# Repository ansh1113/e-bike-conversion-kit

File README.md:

# e-Bike Conversion Kit

## Overview
This project is a custom e-bike conversion kit featuring:
- **STM32-based VESC ESC** for motor control
- **ESP32/ESP8266** for wireless control and battery monitoring
- **36V 10.4Ah Lithium Power Supply** with buck circuits (36V->24V, 24V->12V, 12V->5V)
- **Wireless throttle module** (mode increase/decrease/start switches)
- **GSM/GPS integration** for tracking and security
- **Battery level and mode indicator LEDs**
- **Electronic latch locking system**
- **Phone charging port**

## Features
- Wireless throttle control using ESP32
- Real-time battery monitoring and motor control
- GPS tracking for security
- Compact 4-layer PCB design

## Installation
## 1. Hardware Assembly
- Mount the **VESC ESC** with proper cooling.
- Connect the **36V battery** to the power input.
- Wire the **ESP module** to the ESC for PPM signal transmission.
- Connect **buck converters** for proper voltage regulation.
- Attach **LEDs**, **GSM/GPS module**, and **gyro sensor**.
- Install **wireless throttle module** on the handlebar.

## 2. Software Setup
- Install **VESC Tool** for ESC configuration.
- Flash the **ESP firmware** using Arduino IDE.
- Configure **PPM values** for different speed modes.

# Firmware Installation
## 1. Flashing VESC Firmware
- Download and install **VESC Tool**.
- Connect STM32 to your PC via USB.
- Select the correct **firmware version** and upload.

## 2. Flashing ESP Firmware
- Install **Arduino IDE** with ESP32/ESP8266 support.
- Install necessary libraries (`WiFi`, `TinyGPS++`, `Adafruit_GFX` etc.).
- Compile and upload `Firmware/hook_receiver/hook_receiver.ino`.

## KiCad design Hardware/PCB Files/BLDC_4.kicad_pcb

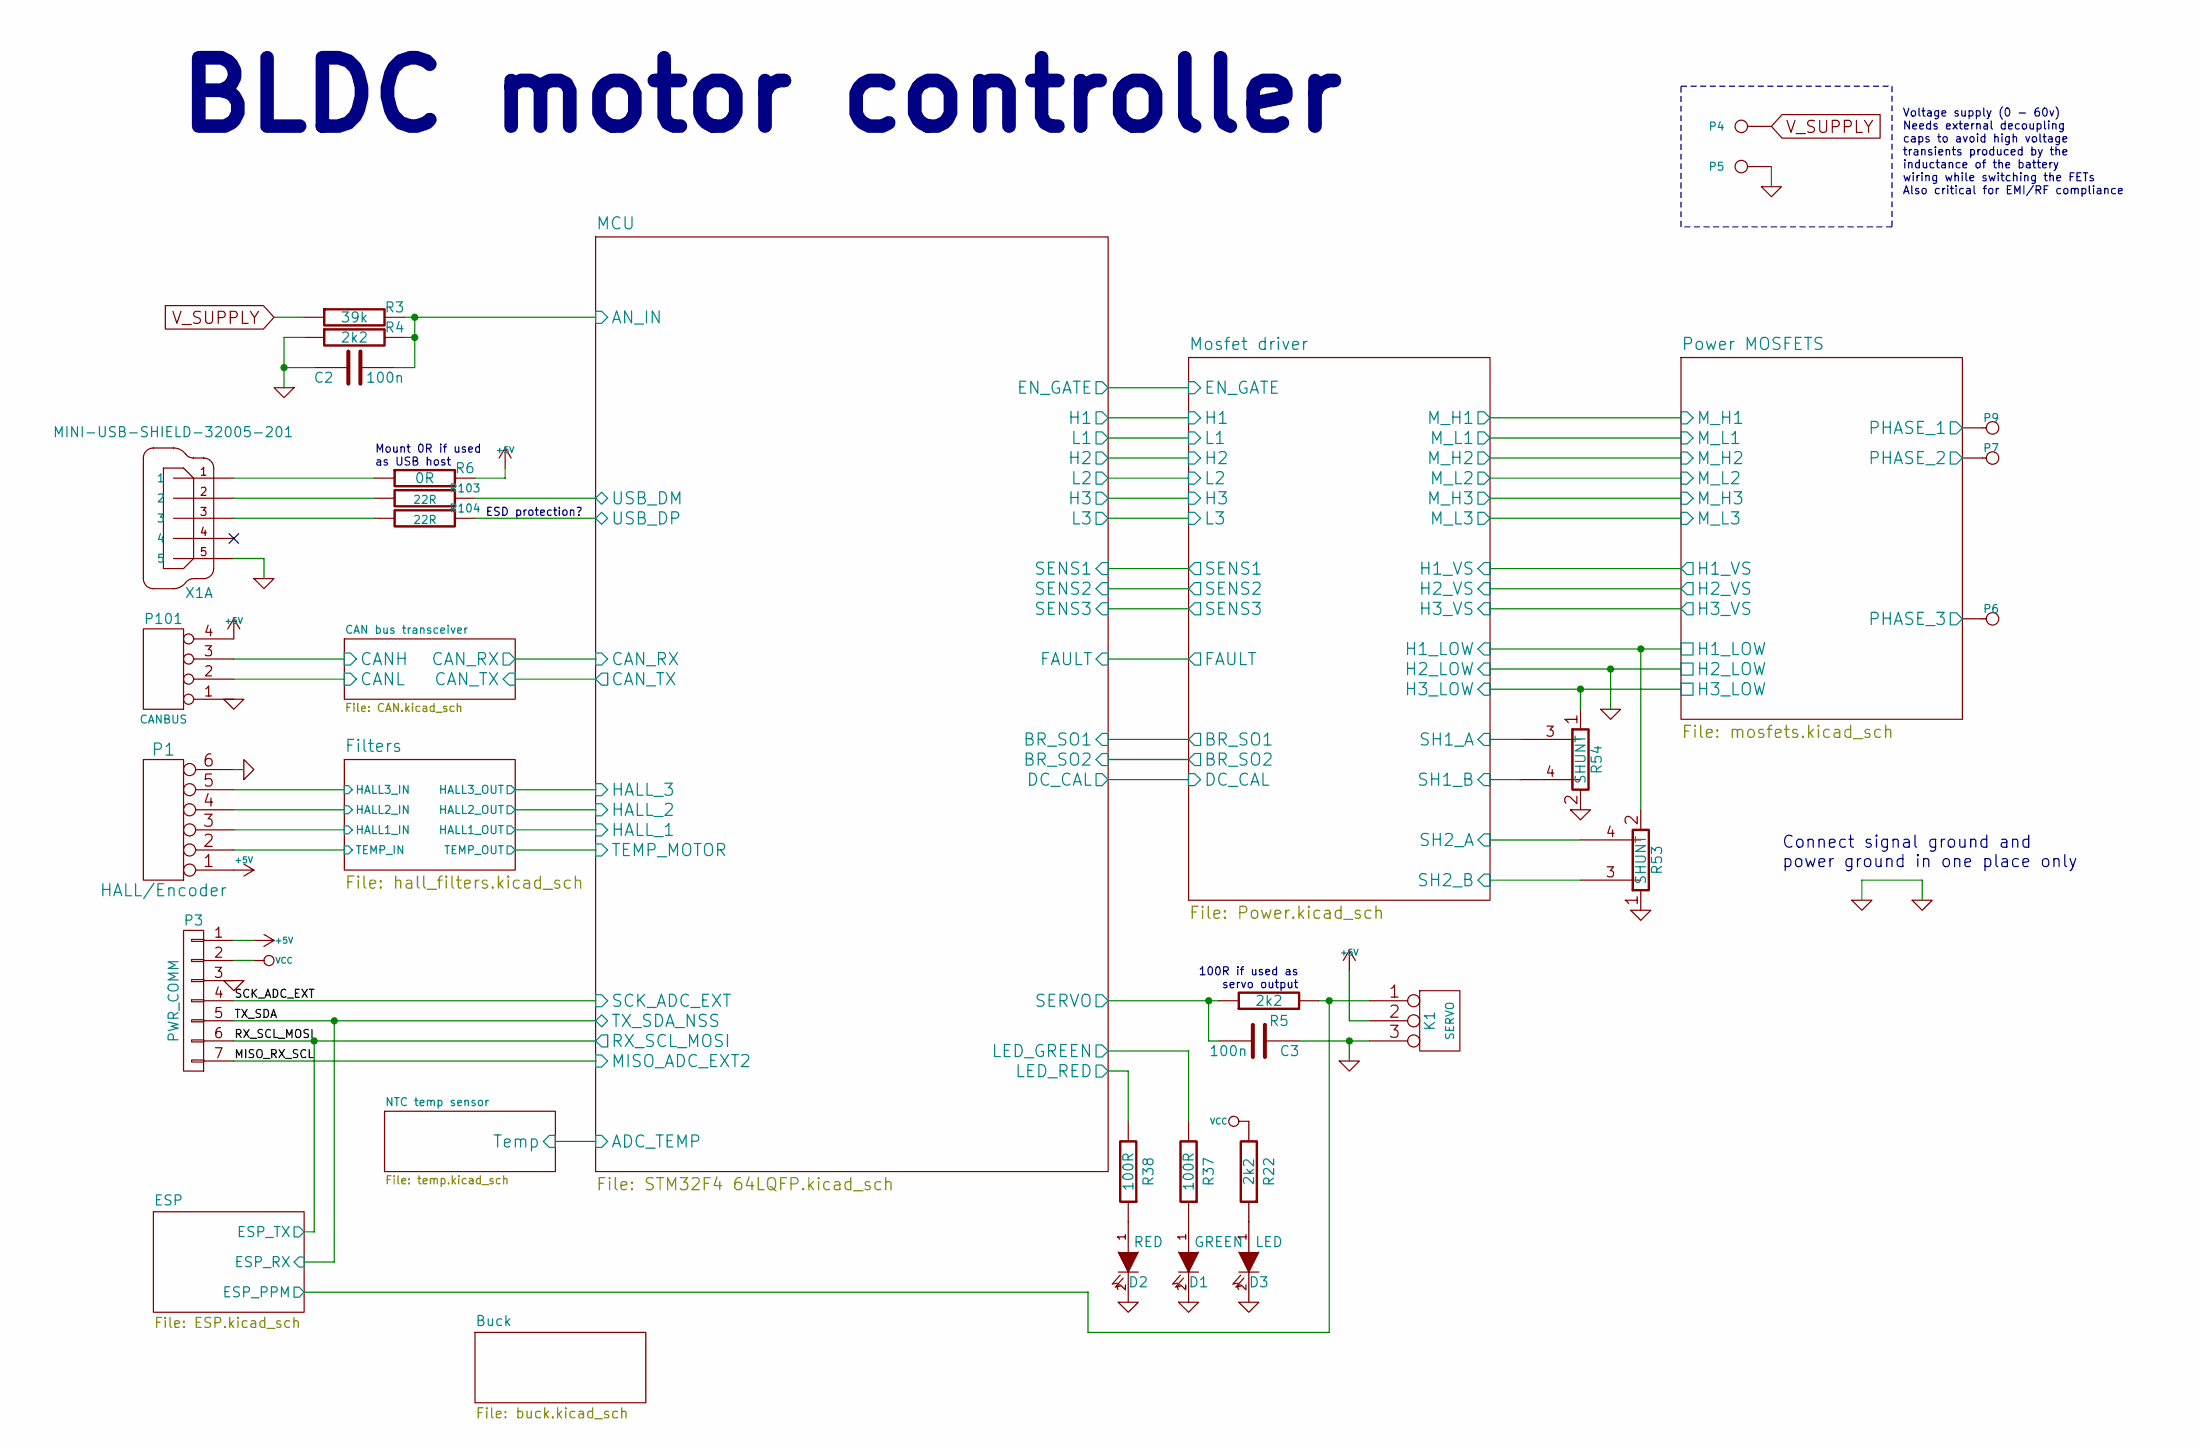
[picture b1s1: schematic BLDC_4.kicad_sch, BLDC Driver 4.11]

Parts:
C2, C3: 100n; SMD-0603_c
D1: GREEN; LED-0603
D2: RED; LED-0603
D3: LED; LED-0603
K1: SERVO; pinhead-1X03
P1: HALL/Encoder; MICRO_JST_6
P3: PWR_COMM; b7b-ph-kl
P4: IN+; 1PAD_4x5mm
P5: IN-; 1PAD_4x5mm
P6: MOTOR1; 1PAD_4x5mm
P7: MOTOR2; 1PAD_4x5mm
P9: MOTOR3; 1PAD_4x5mm
P101: CANBUS; b4b-ph-kl
R3: 39k; SMD-0603_r
R4, R5, R22: 2k2; SMD-0603_r
R6: 0R; SMD-0603_r
R37, R38: 100R; SMD-0603_r
R53, R54: SHUNT; WSLP2726
R103, R104: 22R; SMD-0603_r
X1: MINI-USB-SHIELD-32005-201; USB-UX60R-MB-5ST

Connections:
+5V: K1.2 (PM), P1.1, P3.1, P101.4, R6.2; also elsewhere on the board
/CAN bus transceiver/CANH: P101.3; also elsewhere on the board
/CAN bus transceiver/CANL: P101.2; also elsewhere on the board
/ESP/ESP_PPM: K1.1, R5.2; also elsewhere on the board
/Filters/HALL1_IN: P1.3; also elsewhere on the board
/Filters/HALL2_IN: P1.4; also elsewhere on the board
/Filters/HALL3_IN: P1.5; also elsewhere on the board
/Filters/TEMP_MOTOR: P1.2; also elsewhere on the board
/MCU/AN_IN: C2.2, R3.2, R4.2; also elsewhere on the board
/MCU/LED_GREEN: R37.2; also elsewhere on the board
/MCU/LED_RED: R38.2; also elsewhere on the board
/MCU/SERVO: C3.2, R5.1; also elsewhere on the board
/MCU/USB_DM: R103.1; also elsewhere on the board
/MCU/USB_DP: R104.1; also elsewhere on the board
/MISO_RX_SCL: P3.7; also elsewhere on the board
/Mosfet driver/H1_LOW: R53.2; also elsewhere on the board
/Mosfet driver/H1_VS: P9.1; also elsewhere on the board
/Mosfet driver/H2_VS: P7.1; also elsewhere on the board
/Mosfet driver/H3_LOW: R54.1; also elsewhere on the board
/Mosfet driver/H3_VS: P6.1; also elsewhere on the board
/Mosfet driver/SH1_A: R54.3; also elsewhere on the board
/Mosfet driver/SH1_B: R54.4; also elsewhere on the board
/Mosfet driver/SH2_A: R53.4; also elsewhere on the board
/Mosfet driver/SH2_B: R53.3; also elsewhere on the board
/RX_SCL_MOSI: P3.6; also elsewhere on the board
/SCK_ADC_EXT: P3.4; also elsewhere on the board
/TX_SDA: P3.5; also elsewhere on the board
GND: C2.1, C3.1, D1.2 (K), D2.2 (K), D3.2 (K), K1.3, P1.6, P3.3, P5.1, P101.1, R4.1, R53.1, R54.2, X1.5; also elsewhere on the board
unnamed: D1.1 (A), R37.1
unnamed: D2.1 (A), R38.1
unnamed: D3.1 (A), R22.1
unnamed: R6.1, X1.1
unnamed: R103.2, X1.2
unnamed: R104.2, X1.3
VCC: P3.2, R22.2; also elsewhere on the board
V_SUPPLY: P4.1, R3.1; also elsewhere on the board

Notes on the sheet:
Voltage supply (0 - 60v) Needs external decoupling caps to avoid high voltage transients produced by the inductance of the battery wiring while switching the FETs Also critical for EMI/RF compliance
100R if used as servo output
Mount 0R if used as USB host
BLDC motor controller
Connect signal ground and power ground in one place only
ESD protection?

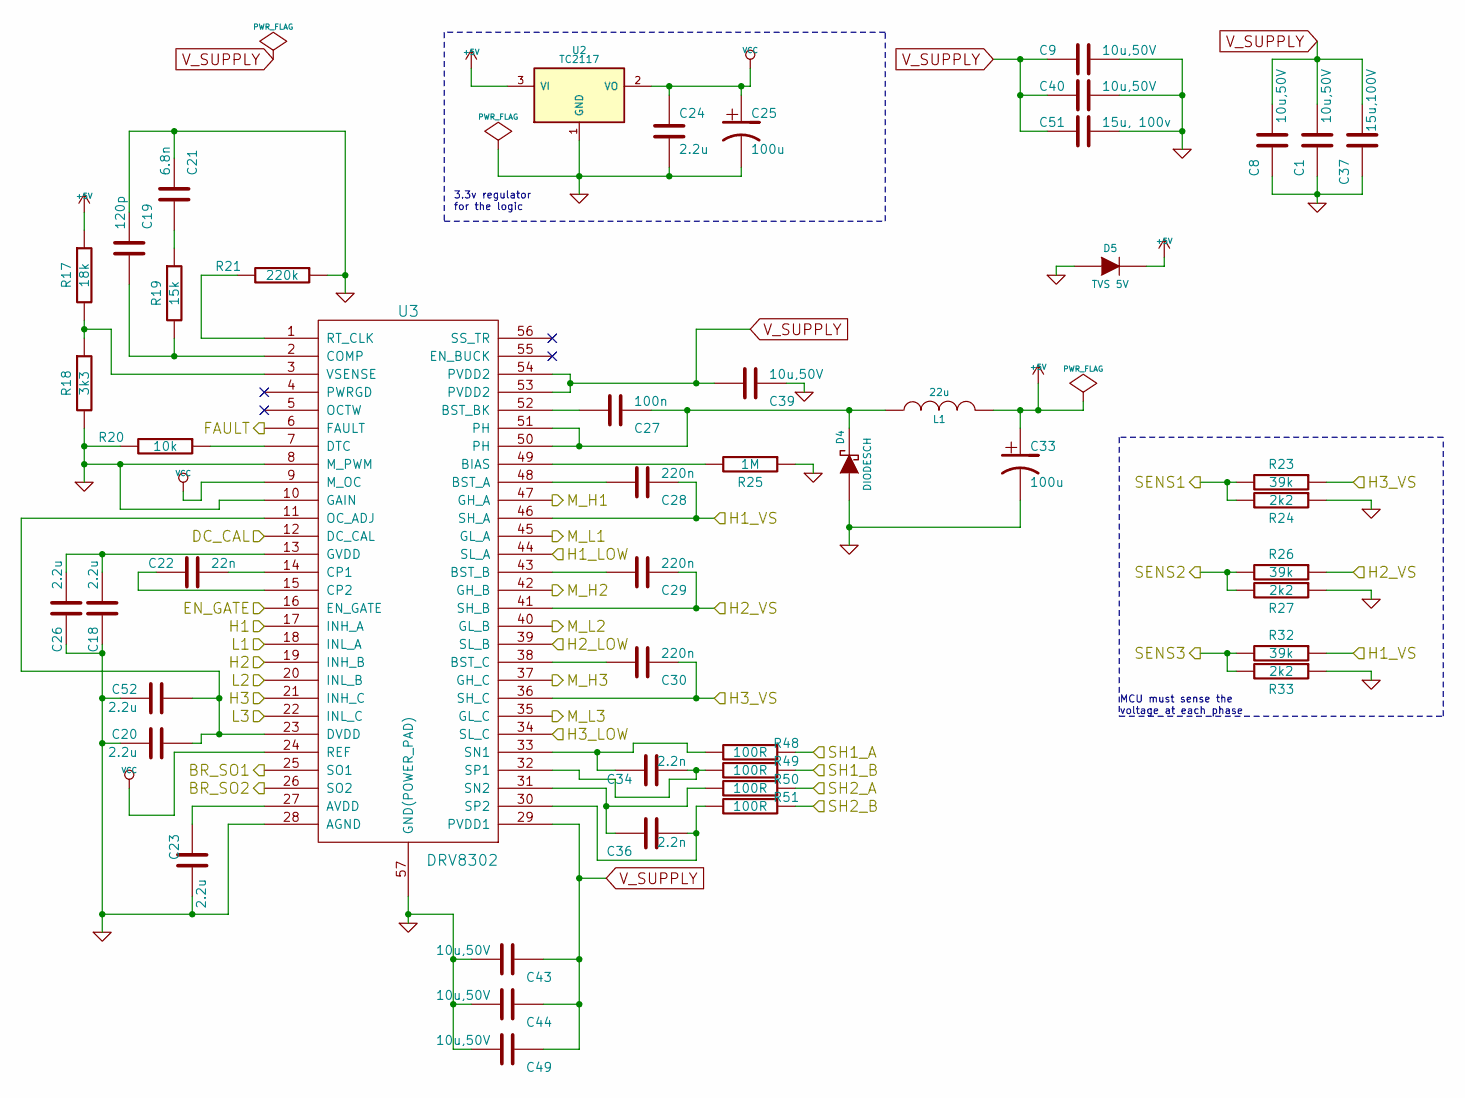
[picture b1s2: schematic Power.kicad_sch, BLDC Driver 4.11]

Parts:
C1, C8, C9, C39, C40, C43, C44, C49: 10u,50V; SMD-1206
C18, C20, C23, C24, C26, C52: 2.2u; SMD-0603_c
C19: 120p; SMD-0603_c
C21: 6.8n; SMD-0603_c
C22: 22n; SMD-0603_c
C25, C33: 100u; c_tant_B
C27: 100n; SMD-0603_c
C28, C29, C30: 220n; SMD-0603_c
C34, C36: 2.2n; SMD-0603_c
C37: 15u,100V; c_2220
C51: 15u, 100v; c_2220
D4: DIODESCH; SMA_Handsoldering
D5: TVS 5V; do214ac
L1: 22u; inductor_smd_8x5mm
R17: 18k; SMD-0603_r
R18: 3k3; SMD-0603_r
R19: 15k; SMD-0603_r
R20: 10k; SMD-0603_r
R21: 220k; SMD-0603_r
R23, R26, R32: 39k; SMD-0603_r
R24, R27, R33: 2k2; SMD-0603_r
R25: 1M; SMD-0603_r
R48, R49, R50, R51: 100R; SMD-0603_r
U2: TC2117; SOT-223
U3: DRV8302; TSSOP-56-PP

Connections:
+5V: C33.1, D5.2 (K), L1.2, R17.1, U2.3 (VI); also elsewhere on the board
/MCU/BR_SO1: U3.25 (SO1); also elsewhere on the board
/MCU/BR_SO2: U3.26 (SO2); also elsewhere on the board
/MCU/DC_CAL: U3.12 (DC_CAL); also elsewhere on the board
/MCU/EN_GATE: U3.16 (EN_GATE); also elsewhere on the board
/MCU/FAULT: U3.6 (FAULT); also elsewhere on the board
/MCU/H1: U3.17 (INH_A); also elsewhere on the board
/MCU/H2: U3.19 (INH_B); also elsewhere on the board
/MCU/H3: U3.21 (INH_C); also elsewhere on the board
/MCU/L1: U3.18 (INL_A); also elsewhere on the board
/MCU/L2: U3.20 (INL_B); also elsewhere on the board
/MCU/L3: U3.22 (INL_C); also elsewhere on the board
/MCU/SENS1: R23.2, R24.2; also elsewhere on the board
/MCU/SENS2: R26.2, R27.2; also elsewhere on the board
/MCU/SENS3: R32.2, R33.2; also elsewhere on the board
/Mosfet driver/H1_LOW: U3.44 (SL_A); also elsewhere on the board
/Mosfet driver/H1_VS: C28.1, R32.1, U3.46 (SH_A); also elsewhere on the board
/Mosfet driver/H2_VS: C29.1, R26.1, U3.41 (SH_B); also elsewhere on the board
/Mosfet driver/H3_LOW: U3.34 (SL_C); also elsewhere on the board
/Mosfet driver/H3_VS: C30.1, R23.1, U3.36 (SH_C); also elsewhere on the board
/Mosfet driver/M_H1: U3.47 (GH_A); also elsewhere on the board
/Mosfet driver/M_H2: U3.42 (GH_B); also elsewhere on the board
/Mosfet driver/M_H3: U3.37 (GH_C); also elsewhere on the board
/Mosfet driver/M_L1: U3.45 (GL_A); also elsewhere on the board
/Mosfet driver/M_L2: U3.40 (GL_B); also elsewhere on the board
/Mosfet driver/M_L3: U3.35 (GL_C); also elsewhere on the board
/Mosfet driver/SH1_A: R48.1; also elsewhere on the board
/Mosfet driver/SH1_B: R49.1; also elsewhere on the board
/Mosfet driver/SH2_A: R50.1; also elsewhere on the board
/Mosfet driver/SH2_B: R51.1; also elsewhere on the board
GND: C1.1, C8.1, C9.1, C18.2, C19.1, C20.1, C21.1, C23.1, C24.2, C25.2, C26.2, C33.2, C37.1, C39.1, C40.1, C43.2, C44.2, C49.2, C51.1, C52.1, D4.1 (A), D5.1 (A), R18.2, R20.2, R21.1, R24.1, R25.1, R27.1, R33.1, U2.1 (GND), U3.8 (M_PWM), U3.10 (GAIN), U3.28 (AGND), U3.39 (SL_B), U3.57 (GND(POWER_PAD)); also elsewhere on the board
unnamed: C21.2, R19.1
unnamed: C27.1, D4.2 (K), L1.1, U3.50 (PH), U3.51 (PH)
unnamed: C23.2, U3.27 (AVDD)
unnamed: R25.2, U3.49 (BIAS)
unnamed: C28.2, U3.48 (BST_A)
unnamed: C29.2, U3.43 (BST_B)
unnamed: C27.2, U3.52 (BST_BK)
unnamed: C30.2, U3.38 (BST_C)
unnamed: C19.2, R19.2, U3.2 (COMP)
unnamed: C22.1, U3.14 (CP1)
unnamed: C22.2, U3.15 (CP2)
unnamed: R20.1, U3.7 (DTC)
unnamed: C20.2, C52.2, U3.11 (OC_ADJ), U3.23 (DVDD)
unnamed: C18.1, C26.1, U3.13 (GVDD)
unnamed: R21.2, U3.1 (RT_CLK)
unnamed: C34.1, R48.2, U3.33 (SN1)
unnamed: C36.1, R50.2, U3.31 (SN2)
unnamed: C34.2, R49.2, U3.32 (SP1)
unnamed: C36.2, R51.2, U3.30 (SP2)
unnamed: R17.2, R18.1, U3.3 (VSENSE)
VCC: C24.1, C25.1, U2.2 (VO), U3.9 (M_OC), U3.24 (REF); also elsewhere on the board
V_SUPPLY: C1.2, C8.2, C9.2, C37.2, C39.2, C40.2, C43.1, C44.1, C49.1, C51.2, U3.29 (PVDD1), U3.53 (PVDD2), U3.54 (PVDD2); also elsewhere on the board

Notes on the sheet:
3.3v regulator for the logic
MCU must sense the voltage at each phase

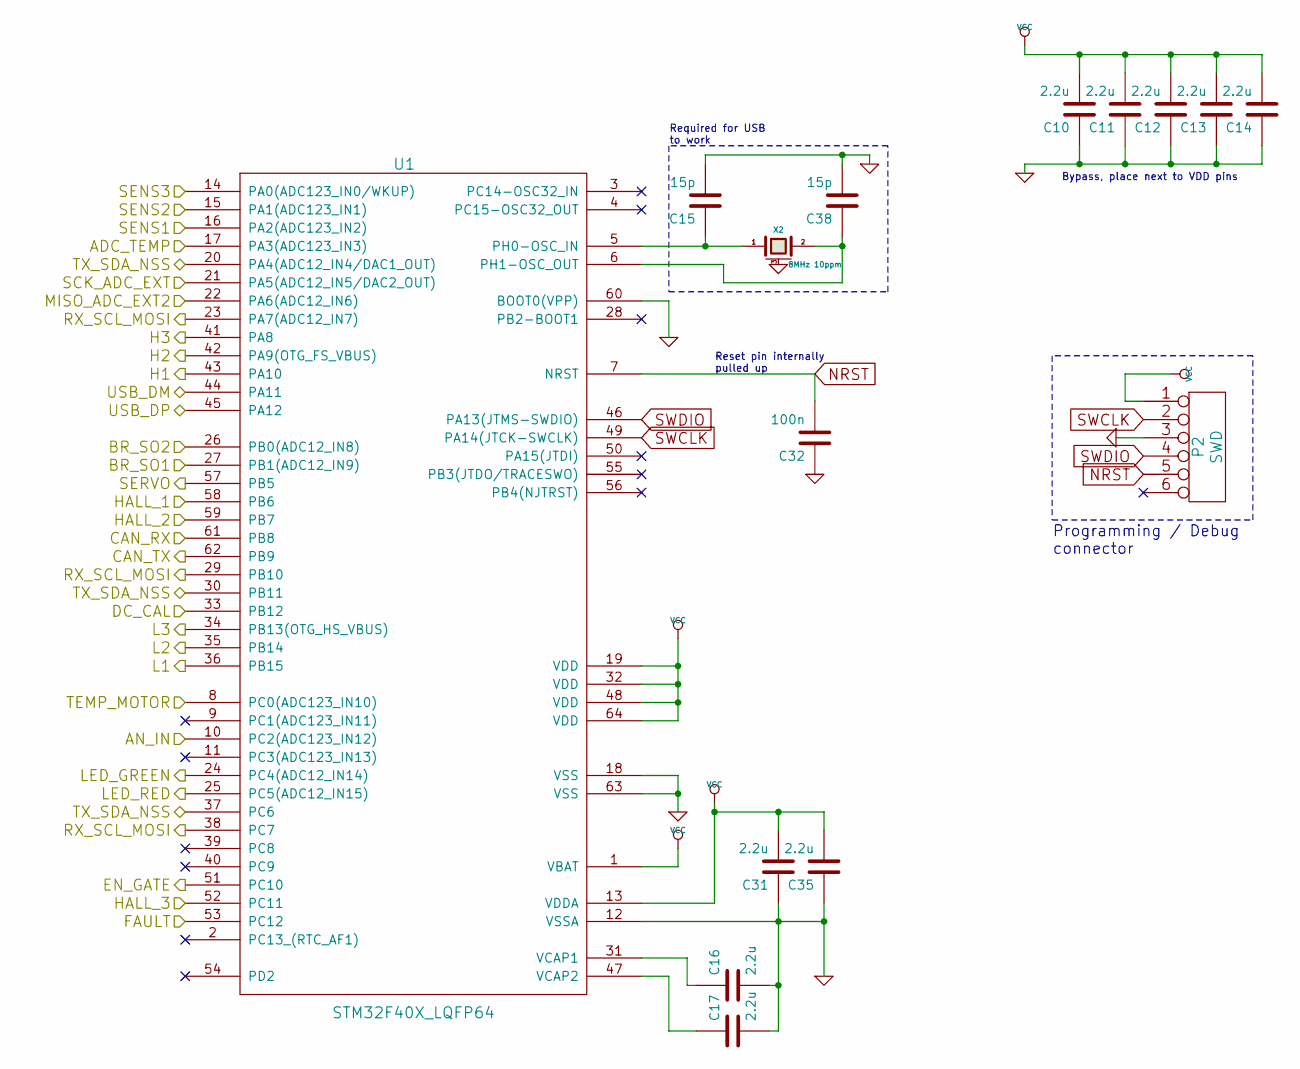
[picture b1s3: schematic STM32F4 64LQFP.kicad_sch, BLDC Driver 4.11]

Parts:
C10, C11, C12, C13, C14, C16, C17, C31, C35: 2.2u; SMD-0603_c
C15, C38: 15p; SMD-0603_c
C32: 100n; SMD-0603_c
P2: SWD; MICRO_JST_6
U1: STM32F40X_LQFP64; lqfp64_pad_mod
X2: 8MHz 10ppm; Crystal_5x3mm; mfg# ABM3B-8.0-10-1UT

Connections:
/CAN bus transceiver/CAN_RX: U1.61 (PB8); also elsewhere on the board
/CAN bus transceiver/CAN_TX: U1.62 (PB9); also elsewhere on the board
/Filters/HALL1_OUT: U1.58 (PB6); also elsewhere on the board
/Filters/HALL2_OUT: U1.59 (PB7); also elsewhere on the board
/Filters/HALL3_OUT: U1.52 (PC11); also elsewhere on the board
/Filters/TEMP_MOTOR: U1.8 (PC0(ADC123_IN10)); also elsewhere on the board
/MCU/ADC_TEMP: U1.17 (PA3(ADC123_IN3)); also elsewhere on the board
/MCU/AN_IN: U1.10 (PC2(ADC123_IN12)); also elsewhere on the board
/MCU/BR_SO1: U1.27 (PB1(ADC12_IN9)); also elsewhere on the board
/MCU/BR_SO2: U1.26 (PB0(ADC12_IN8)); also elsewhere on the board
/MCU/DC_CAL: U1.33 (PB12); also elsewhere on the board
/MCU/EN_GATE: U1.51 (PC10); also elsewhere on the board
/MCU/FAULT: U1.53 (PC12); also elsewhere on the board
/MCU/H1: U1.43 (PA10); also elsewhere on the board
/MCU/H2: U1.42 (PA9(OTG_FS_VBUS)); also elsewhere on the board
/MCU/H3: U1.41 (PA8); also elsewhere on the board
/MCU/L1: U1.36 (PB15); also elsewhere on the board
/MCU/L2: U1.35 (PB14); also elsewhere on the board
/MCU/L3: U1.34 (PB13(OTG_HS_VBUS)); also elsewhere on the board
/MCU/LED_GREEN: U1.24 (PC4(ADC12_IN14)); also elsewhere on the board
/MCU/LED_RED: U1.25 (PC5(ADC12_IN15)); also elsewhere on the board
/MCU/SENS1: U1.16 (PA2(ADC123_IN2)); also elsewhere on the board
/MCU/SENS2: U1.15 (PA1(ADC123_IN1)); also elsewhere on the board
/MCU/SENS3: U1.14 (PA0(ADC123_IN0/WKUP)); also elsewhere on the board
/MCU/SERVO: U1.57 (PB5); also elsewhere on the board
/MCU/USB_DM: U1.44 (PA11); also elsewhere on the board
/MCU/USB_DP: U1.45 (PA12); also elsewhere on the board
/MISO_RX_SCL: U1.22 (PA6(ADC12_IN6)); also elsewhere on the board
/RX_SCL_MOSI: U1.23 (PA7(ADC12_IN7)), U1.29 (PB10), U1.38 (PC7); also elsewhere on the board
/SCK_ADC_EXT: U1.21 (PA5(ADC12_IN5/DAC2_OUT)); also elsewhere on the board
/TX_SDA: U1.20 (PA4(ADC12_IN4/DAC1_OUT)), U1.30 (PB11), U1.37 (PC6); also elsewhere on the board
GND: C10.1, C11.1, C12.1, C13.1, C14.1, C15.2, C16.2, C17.2, C31.1, C32.1, C35.1, C38.2, P2.3, U1.12 (VSSA), U1.18 (VSS), U1.60 (BOOT0(VPP)), U1.63 (VSS), X2.3 (case); also elsewhere on the board
NRST: C32.2, P2.5, U1.7 (NRST)
unnamed: C15.1, U1.5 (PH0-OSC_IN), X2.1
unnamed: C38.1, U1.6 (PH1-OSC_OUT), X2.2
unnamed: C16.1, U1.31 (VCAP1)
unnamed: C17.1, U1.47 (VCAP2)
SWCLK: P2.2, U1.49 (PA14(JTCK-SWCLK))
SWDIO: P2.4, U1.46 (PA13(JTMS-SWDIO))
VCC: C10.2, C11.2, C12.2, C13.2, C14.2, C31.2, C35.2, P2.1, U1.1 (VBAT), U1.13 (VDDA), U1.19 (VDD), U1.32 (VDD), U1.48 (VDD), U1.64 (VDD); also elsewhere on the board

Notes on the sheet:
Reset pin internally pulled up
Programming / Debug connector
Required for USB to work
Bypass, place next to VDD pins

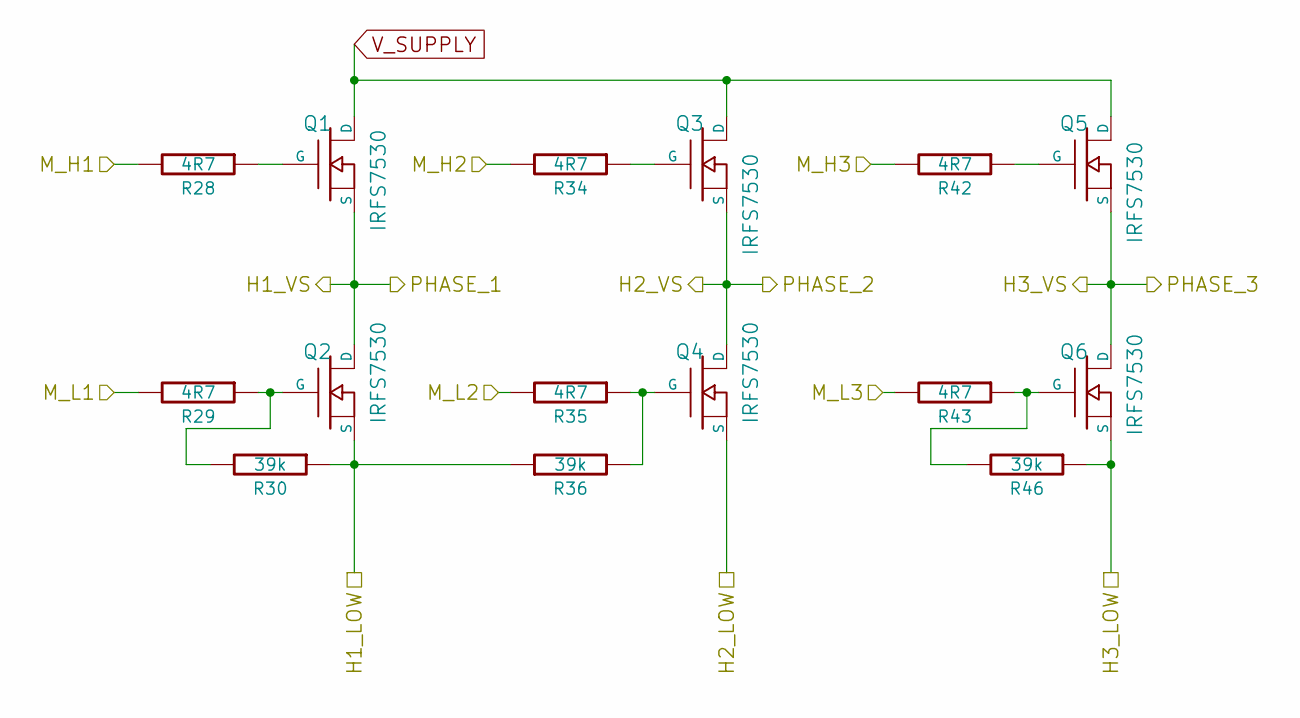
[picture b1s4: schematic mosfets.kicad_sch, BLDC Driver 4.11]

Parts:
Q1, Q2, Q3, Q4, Q5, Q6: IRFS7530; D2PAK-7-GDS
R28, R29, R34, R35, R42, R43: 4R7; SMD-0603_r
R30, R36, R46: 39k; SMD-0603_r

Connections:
/Mosfet driver/H1_LOW: Q2.S, R30.1, R36.1; also elsewhere on the board
/Mosfet driver/H1_VS: Q1.S, Q2.D; also elsewhere on the board
/Mosfet driver/H2_VS: Q3.S, Q4.D; also elsewhere on the board
/Mosfet driver/H3_LOW: Q6.S, R46.1; also elsewhere on the board
/Mosfet driver/H3_VS: Q5.S, Q6.D; also elsewhere on the board
/Mosfet driver/M_H1: R28.2; also elsewhere on the board
/Mosfet driver/M_H2: R34.2; also elsewhere on the board
/Mosfet driver/M_H3: R42.2; also elsewhere on the board
/Mosfet driver/M_L1: R29.2; also elsewhere on the board
/Mosfet driver/M_L2: R35.2; also elsewhere on the board
/Mosfet driver/M_L3: R43.2; also elsewhere on the board
GND: Q4.S; also elsewhere on the board
unnamed: Q1.G, R28.1
unnamed: Q2.G, R29.1, R30.2
unnamed: Q3.G, R34.1
unnamed: Q4.G, R35.1, R36.2
unnamed: Q5.G, R42.1
unnamed: Q6.G, R43.1, R46.2
V_SUPPLY: Q1.D, Q3.D, Q5.D; also elsewhere on the board

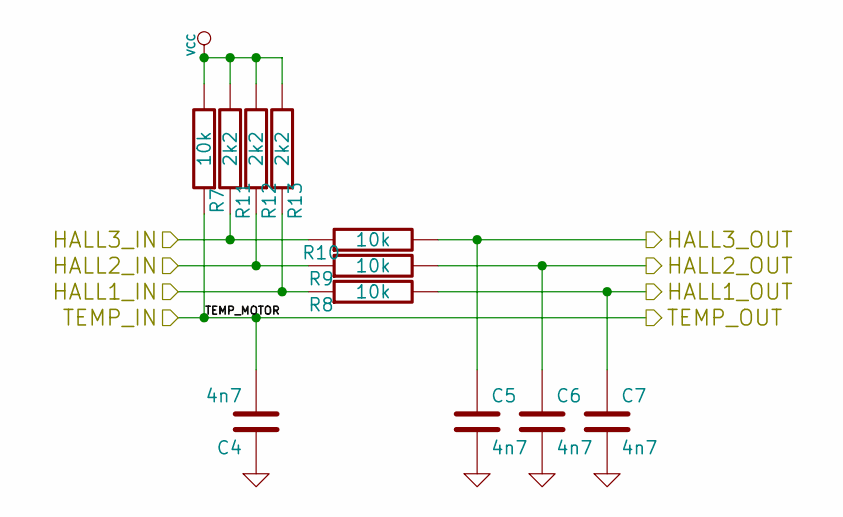
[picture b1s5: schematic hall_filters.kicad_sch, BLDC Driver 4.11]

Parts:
C4, C5, C6, C7: 4n7; SMD-0603_c
R7, R8, R9, R10: 10k; SMD-0603_r
R11, R12, R13: 2k2; SMD-0603_r

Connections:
/Filters/HALL1_IN: R8.1, R13.1; also elsewhere on the board
/Filters/HALL1_OUT: C7.1, R8.2; also elsewhere on the board
/Filters/HALL2_IN: R9.1, R12.1; also elsewhere on the board
/Filters/HALL2_OUT: C6.1, R9.2; also elsewhere on the board
/Filters/HALL3_IN: R10.1, R11.1; also elsewhere on the board
/Filters/HALL3_OUT: C5.1, R10.2; also elsewhere on the board
/Filters/TEMP_MOTOR: C4.2, R7.1; also elsewhere on the board
GND: C4.1, C5.2, C6.2, C7.2; also elsewhere on the board
VCC: R7.2, R11.2, R12.2, R13.2; also elsewhere on the board

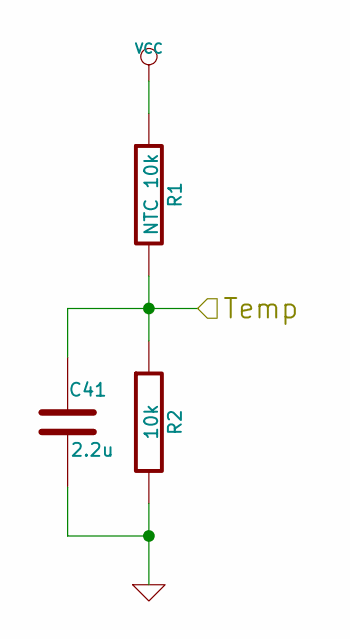
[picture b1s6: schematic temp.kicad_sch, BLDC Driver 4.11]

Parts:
C41: 2.2u; SMD-0603_c
R1: NTC 10k; SMD-0603_r
R2: 10k; SMD-0603_r

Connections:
/MCU/ADC_TEMP: C41.1, R1.2, R2.1; also elsewhere on the board
GND: C41.2, R2.2; also elsewhere on the board
VCC: R1.1; also elsewhere on the board

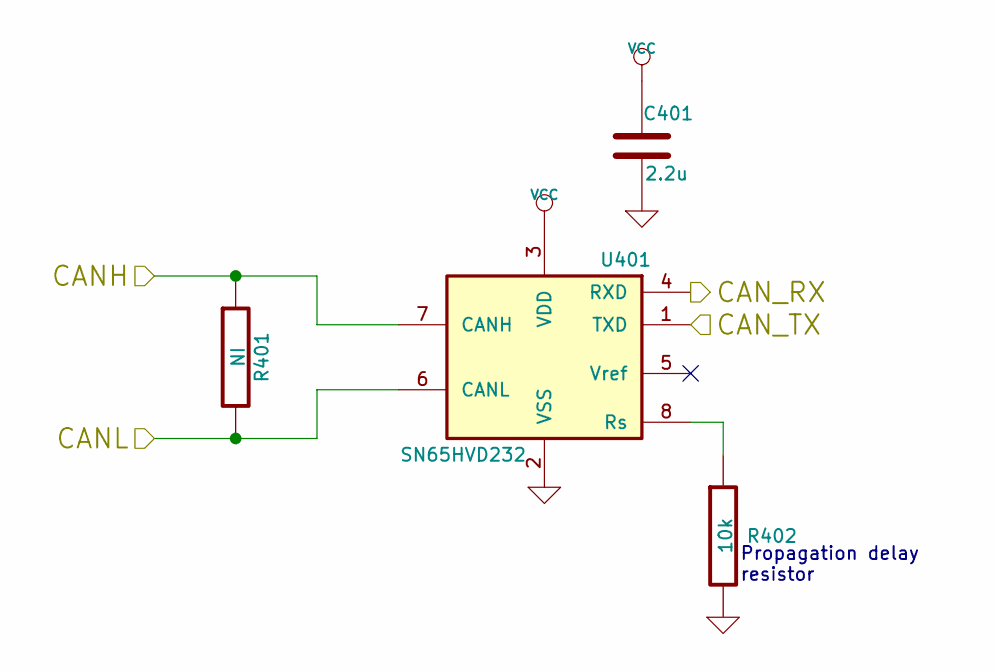
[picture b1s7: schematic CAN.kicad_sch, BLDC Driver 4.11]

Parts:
C401: 2.2u; SMD-0603_c
R401: NI; SMD-0603_r
R402: 10k; SMD-0603_r
U401: SN65HVD232; SOIC-8-W

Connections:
/CAN bus transceiver/CANH: R401.1, U401.7 (CANH); also elsewhere on the board
/CAN bus transceiver/CANL: R401.2, U401.6 (CANL); also elsewhere on the board
/CAN bus transceiver/CAN_RX: U401.4 (RXD); also elsewhere on the board
/CAN bus transceiver/CAN_TX: U401.1 (TXD); also elsewhere on the board
GND: C401.2, R402.2, U401.2 (VSS); also elsewhere on the board
unnamed: R402.1, U401.8 (Rs)
VCC: C401.1, U401.3 (VDD); also elsewhere on the board

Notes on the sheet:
Propagation delay resistor

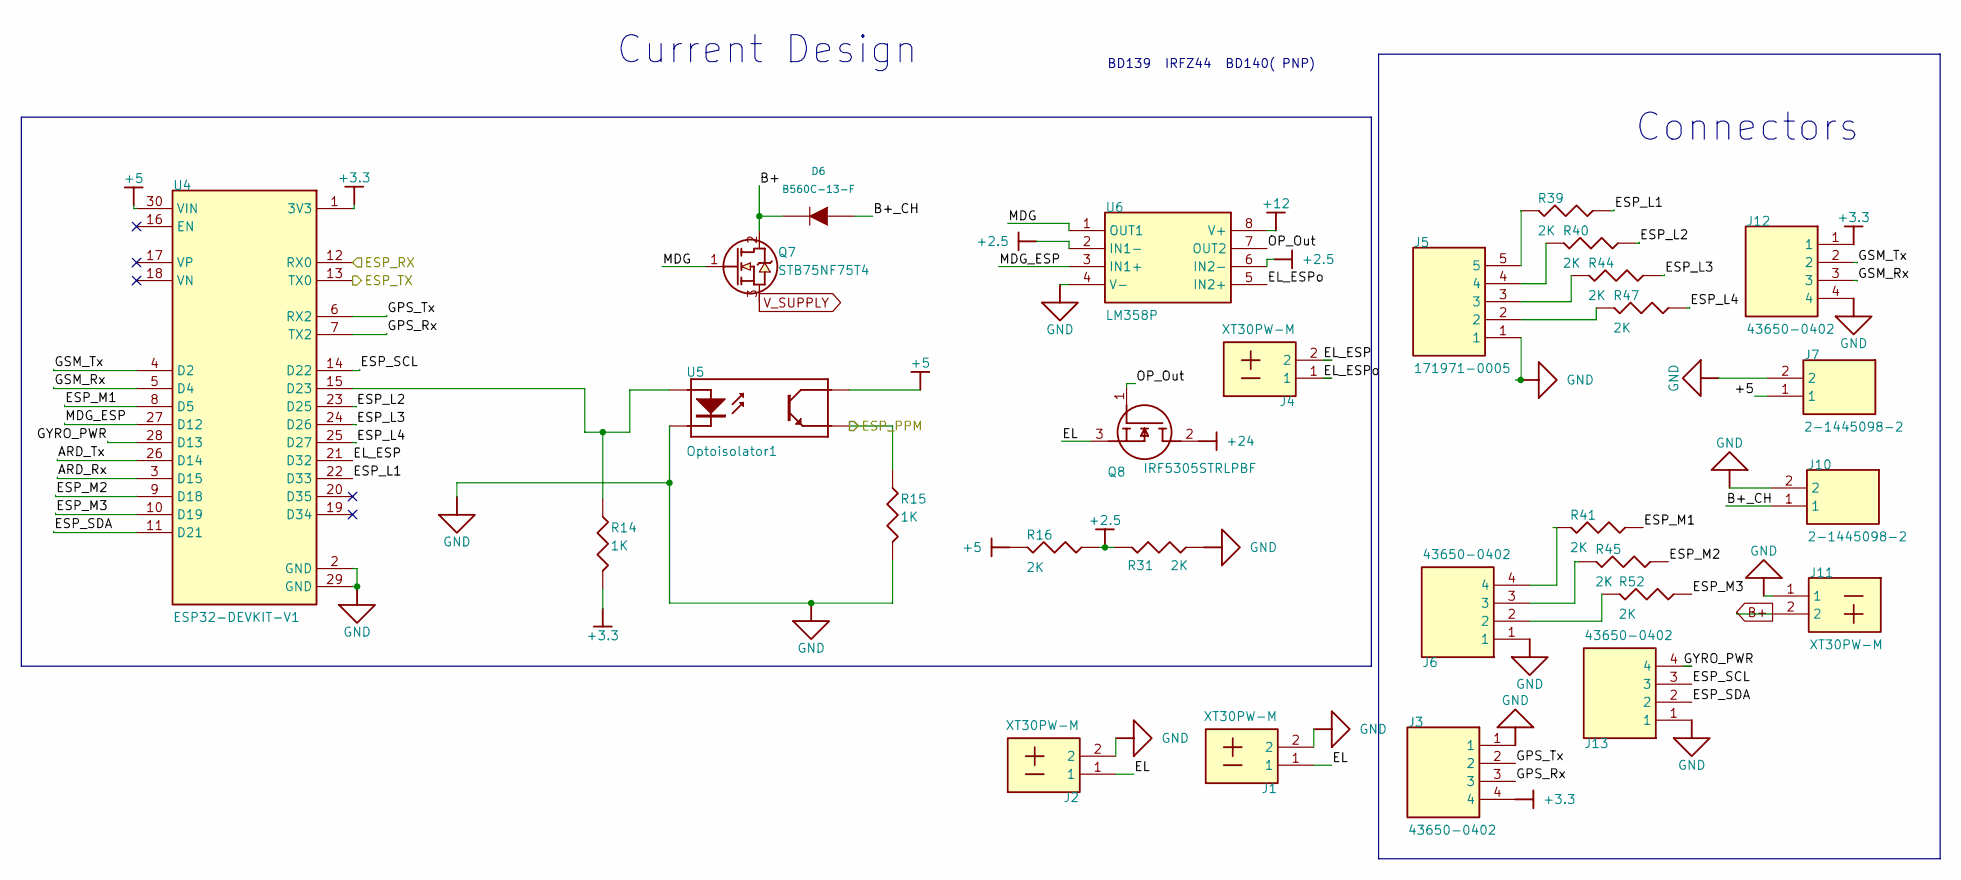
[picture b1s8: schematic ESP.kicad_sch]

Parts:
D6: B560C-13-F
J1, J2, J4: XT30PW-M; JST_EH_B2B-EH-A_1x02_P2.50mm_Vertical; MANUFACTURER_PART_NUMBER XT30PW-M
J3, J6, J12, J13: 43650-0402; JST_EH_B4B-EH-A_1x04_P2.50mm_Vertical; MANUFACTURER_PART_NUMBER 43650-0402; MOUSER PART NUMBER 538-43650-0402
J5: 171971-0005; JST_EH_B5B-EH-A_1x05_P2.50mm_Vertical; MANUFACTURER_PART_NUMBER 171971-0005; MOUSER PART NUMBER 538-171971-0005
J7, J10: 2-1445098-2; AMASS_XT30U-F_1x02_P5.0mm_Vertical; MANUFACTURER_PART_NUMBER 2-1445098-2; MOUSER PART NUMBER 571-2-1445098-2
J11: XT30PW-M; AMASS_XT30U-F_1x02_P5.0mm_Vertical; MANUFACTURER_PART_NUMBER XT30PW-M
Q7: STB75NF75T4; VREG_L7805ACD2T
Q8: IRF5305STRLPBF; TRANS_IRF3205S; MANUFACTURER_PART_NUMBER IRF1407PBF; MOUSER PART NUMBER 942-IRF1407PBF
R14: 1k; R_1210_3225Metric
R15: 1K; R_1210_3225Metric
R16, R31: 2k; R_1210_3225Metric
R39, R40, R41, R44, R45, R47, R52: 2K; R_1210_3225Metric
U4: ESP32-DEVKIT-V1; MODULE_ESP32_DEVKIT_V1
U5: Optoisolator1; DIP-4_W7.62mm_Socket
U6: LM358P; DIP-8_W7.62mm_Socket; MANUFACTURER_PART_NUMBER LM358P; MOUSER PART NUMBER 595-LM358P

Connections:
+2.5: R16.1, R31.2, U6.2 (IN1-), U6.6 (IN2-)
+3.3: J3.4, J12.1, R14.2, U4.1 (3V3)
+5: J7.1, R16.2, U4.30 (VIN), U5.4 (C); also elsewhere on the board
+12: U6.8 (V+); also elsewhere on the board
+24: Q8.2 (D); also elsewhere on the board
/ESP/ARD_Rx: U4.3 (D15)
/ESP/ARD_Tx: U4.26 (D14)
/ESP/B+_CH: D6.1 (A), J10.1
/ESP/EL: J1.1, J2.1, Q8.3 (S)
/ESP/EL_ESP: J4.2, U4.21 (D32)
/ESP/EL_ESPo: J4.1, U6.5 (IN2+)
/ESP/ESP_L1: R39.1, U4.22 (D33)
/ESP/ESP_L2: R40.1, U4.23 (D25)
/ESP/ESP_L3: R44.1, U4.24 (D26)
/ESP/ESP_L4: R47.1, U4.25 (D27)
/ESP/ESP_M1: R41.1, U4.8 (D5)
/ESP/ESP_M2: R45.1, U4.9 (D18)
/ESP/ESP_M3: R52.1, U4.10 (D19)
/ESP/ESP_PPM: R15.1, U5.3 (E); also elsewhere on the board
/ESP/ESP_SCL: J13.3, U4.14 (D22)
/ESP/ESP_SDA: J13.2, U4.11 (D21)
/ESP/GPS_Rx: J3.3, U4.7 (TX2)
/ESP/GPS_Tx: J3.2, U4.6 (RX2)
/ESP/GSM_Rx: J12.3, U4.5 (D4)
/ESP/GSM_Tx: J12.2, U4.4 (D2)
/ESP/GYRO_PWR: J13.4, U4.28 (D13)
/ESP/MDG: Q7.1 (G), U6.1 (OUT1)
/ESP/MDG_ESP: U4.27 (D12), U6.3 (IN1+)
/ESP/OP_Out: Q8.1 (G), U6.7 (OUT2)
/RX_SCL_MOSI: U4.13 (TX0); also elsewhere on the board
/TX_SDA: U4.12 (RX0); also elsewhere on the board
B+: D6.2 (K), J11.2, Q7.2 (D); also elsewhere on the board
GND: J1.2, J2.2, J3.1, J5.1, J6.1, J7.2, J10.2, J11.1, J12.4, J13.1, R15.2, R31.1, U4.2 (GND), U4.29 (GND), U5.2 (K), U6.4 (V-); also elsewhere on the board
unnamed: J5.2, R47.2
unnamed: J5.3, R44.2
unnamed: J5.4, R40.2
unnamed: J5.5, R39.2
unnamed: J6.2, R52.2
unnamed: J6.3, R45.2
unnamed: J6.4, R41.2
unnamed: R14.1, U4.15 (D23), U5.1 (A)
V_SUPPLY: Q7.3 (S); also elsewhere on the board

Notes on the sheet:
BD139 IRFZ44 BD140( PNP)
Current Design
Connectors

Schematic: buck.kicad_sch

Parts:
C42, C50, C53: EEE1HA101UAP; CAP_EEE1HA101UAP; PARTREV 10-Oct-19; DigiKey_Part_Number PCE4610TR-ND
C45: T527T226M025ATE100; CP_EIA-7343-31_Kemet-D
C46: LMJ316BB7226KLHT; C_1206_3216Metric
C47, C48, C55: KAM21BR71H104JT; C_0805_2012Metric
C54: MAASL105CD7105MFCA01; C_0402_1005Metric
D7: SS34; DIO_SS34
F1, F2: 3403.0176.24; Fuse_Schurter_UMT250
J14: XT30PW-M; AMASS_XT30U-F_1x02_P5.0mm_Vertical; MANUFACTURER_PART_NUMBER XT30PW-M
L2: AMDLA4020S-220MT; IND_AMDLA4020S-220MT; PARTREV 9/16/2019
L3: SRN6045TA-220M; IND_SRN6045TA-220M; PARTREV 2018-10
L4: SPM6530T-6R8M; IND_SPM6530T-6R8M-HZ; PARTREV 9/16/2019
R55: 18.2kΩ; R_1210_3225Metric
R56, R59: 2.2kΩ; R_1210_3225Metric
R57: 210kΩ; R_1210_3225Metric
R58: 40.2kΩ; R_1210_3225Metric
R60: 39kΩ; R_1210_3225Metric
U7, U9: LM22678TJ-ADJ/NOPB; LM22678TJ-ADJNOPB; MPN LM22670TJ-ADJ/NOPB
U8: MP1584EN-LF-Z; MP1584(1)

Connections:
+5: C46.2, C48.2, J14.2, L3.2, R57.2; also elsewhere on the board
+12: C45.2, L2.2, R55.2; also elsewhere on the board
+24: C53.1, C54.1, L4.2, R60.2; also elsewhere on the board
/Buck/SW: D7.2 (A), L3.1, U8.1 (SW)
B+: F1.1, F2.1; also elsewhere on the board
GND: C46.1, C47.2, C48.1, C53.2, C54.2, D7.1 (K), J14.1, R56.1, R58.1, R59.1, U7.4 (GND), U7.8 (EPAD), U8.5 (GND), U8.9 (EP), U9.4 (GND), U9.8 (EPAD); also elsewhere on the board
unnamed: C42.1, F1.2
unnamed: C50.1, F2.2
unnamed: R55.1, R56.2, U7.6 (FB)
unnamed: L2.1, U7.1 (SW)
unnamed: C42.2, U7.2 (VIN)
unnamed: R57.1, R58.2, U8.4 (FB)
unnamed: C45.1, C47.1, U8.7 (VIN)
unnamed: C55.1, U9.3 (BOOT)
unnamed: R59.2, R60.1, U9.6 (FB)
unnamed: C55.2, L4.1, U9.1 (SW)
unnamed: C50.2, U9.2 (VIN)
